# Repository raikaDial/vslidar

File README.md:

# vslidar
A Low-Cost 3D Multi-LIDAR System for ROS

Future site of developed hardware, software, and firmware.

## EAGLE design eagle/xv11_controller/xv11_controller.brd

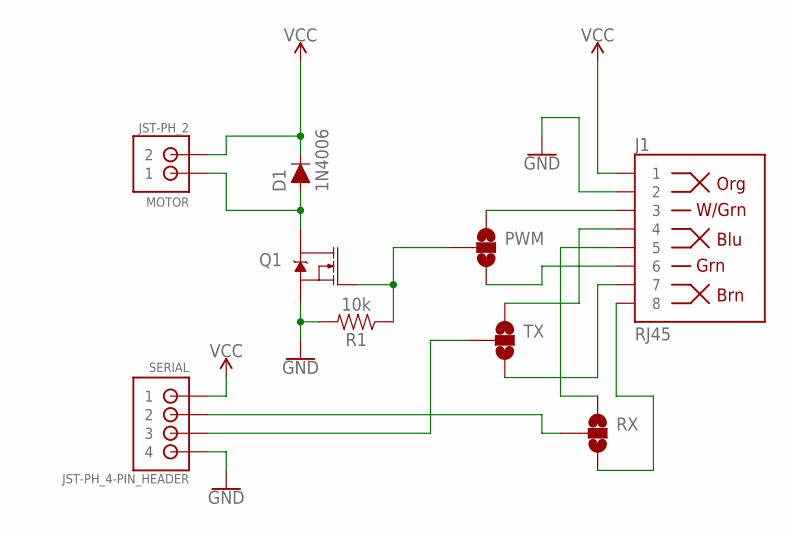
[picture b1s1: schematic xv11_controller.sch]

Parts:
D1: 1N4006; DIODE-1N4001
J1: RJ45; RJ45-8
MOTOR: JST-PH_2; JST_B2B-PH_HEADER
PWM: JUMPER-SMT_3_NO_NO-SILK; SMT-JUMPER_3_NO_NO-SILK
Q1: MOSFET-NCH-FQP30N06L; TO220V
R1: 10k; AXIAL-0.3
RX: JUMPER-SMT_3_NO_NO-SILK; SMT-JUMPER_3_NO_NO-SILK
SERIAL: JST-PH_4-PIN_HEADER; JST_B4B-PH_HEADER
TX: JUMPER-SMT_3_NO_NO-SILK; SMT-JUMPER_3_NO_NO-SILK

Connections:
GND: J1.2, Q1.3 (S), R1.P$2 (2), SERIAL.P4 (4)
unnamed: PWM.2, Q1.1 (G), R1.P$1 (1)
unnamed: D1.A, MOTOR.P1 (1), Q1.2 (D)
unnamed: J1.3, PWM.1
unnamed: J1.6, PWM.3
unnamed: J1.4, TX.1
unnamed: J1.7, TX.3
unnamed: J1.5, RX.1
unnamed: J1.8, RX.3
RX: RX.2, SERIAL.P2 (2)
TX: SERIAL.P3 (3), TX.2
VCC: D1.C, J1.1, MOTOR.P2 (2), SERIAL.P1 (1)

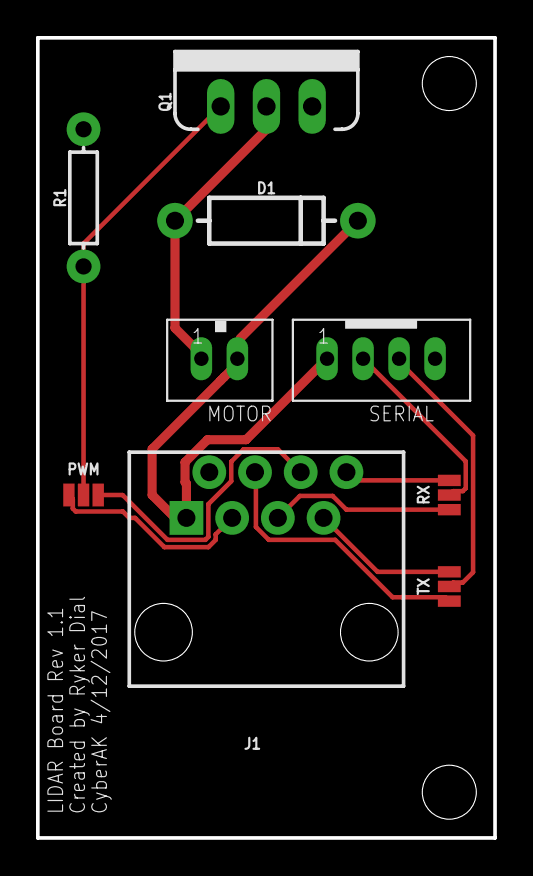
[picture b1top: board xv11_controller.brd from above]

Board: 2 copper layers, 25.4 x 44.5 mm, 9 parts (0 on the bottom side), 12 nets.

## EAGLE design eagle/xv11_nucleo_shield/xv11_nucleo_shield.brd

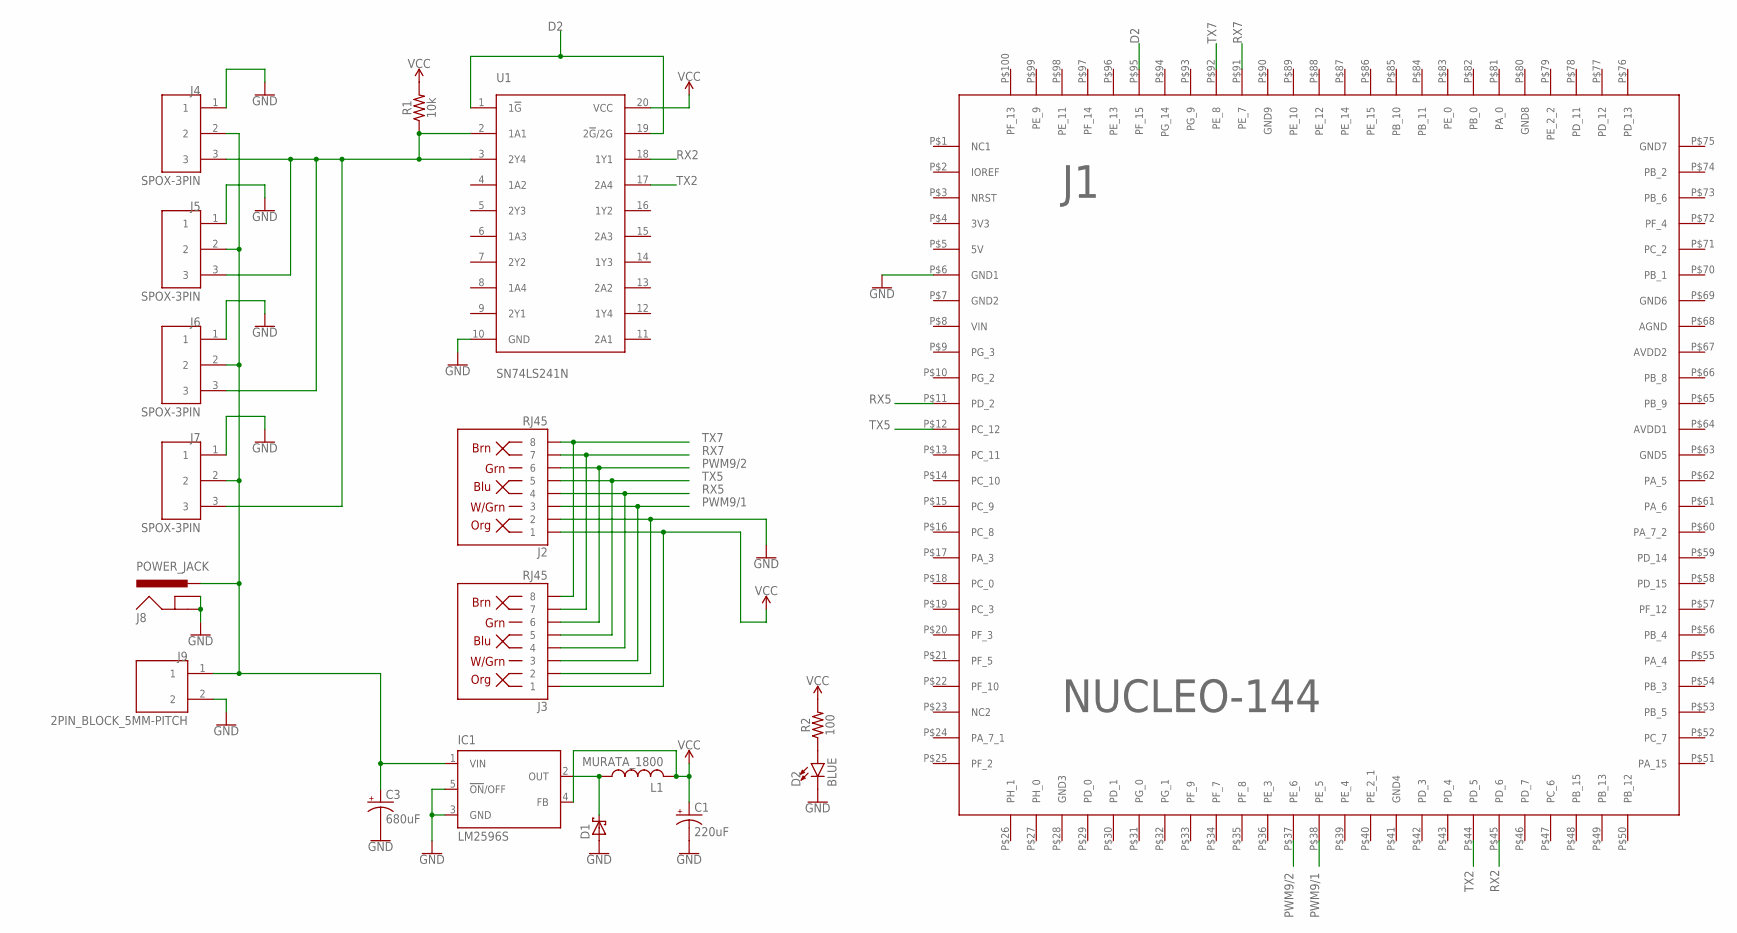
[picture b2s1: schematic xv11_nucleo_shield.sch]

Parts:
C1: 220uF; CPOL-RADIAL-2.5MM-6.5MM
C3: 680uF; EEU-FR1C681L
D1: SCHOTTKY-DIODEDO201T15; DO201T15
D2: BLUE; LED-1206
IC1: LM2596S; TO263-5
J1: NUCLEO-144
J2, J3: RJ45; RJ45-8
J4, J5, J6, J7: SPOX-3PIN
J8: POWER_JACK; POWER_JACK_PTH
J9: 2PIN_BLOCK_5MM-PITCH
L1: MURATA_1800
R1: 10k; AXIAL-0.3
R2: 100; AXIAL-0.3
U1: SN74LS241N; DIL20

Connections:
D2: J1.P$95 (PF_15), U1.1 (1!G), U1.19 (2!G!/2G)
GND: C1.2 (-), C3.P$2 (-), D1.A, D2.C, IC1.3 (GND), IC1.5 (!ON!/OFF), J1.P$6 (GND1), J2.2, J3.2, J4.1, J5.1, J6.1, J7.1, J8.GND, J8.GNDBREAK, J9.2, U1.10 (GND)
unnamed: J4.3, J5.3, J6.3, J7.3, R1.P$1 (1), U1.2 (1A1), U1.3 (2Y4)
unnamed: C3.P$1 (+), IC1.1 (VIN), J4.2, J5.2, J6.2, J7.2, J8.PWR, J9.1
unnamed: D1.C, IC1.2 (OUT), L1.P$1 (1)
unnamed: D2.A, R2.P$1 (1)
PWM9/1: J1.P$38 (PE_5), J2.3, J3.3
PWM9/2: J1.P$37 (PE_6), J2.6, J3.6
RX2: J1.P$45 (PD_6), U1.18 (1Y1)
RX5: J1.P$11 (PD_2), J2.4, J3.4
RX7: J1.P$91 (PE_7), J2.7, J3.7
TX2: J1.P$44 (PD_5), U1.17 (2A4)
TX5: J1.P$12 (PC_12), J2.5, J3.5
TX7: J1.P$92 (PE_8), J2.8, J3.8
VCC: C1.1 (+), IC1.4 (FB), J2.1, J3.1, L1.P$2 (2), R1.P$2 (2), R2.P$2 (2), U1.20 (VCC)

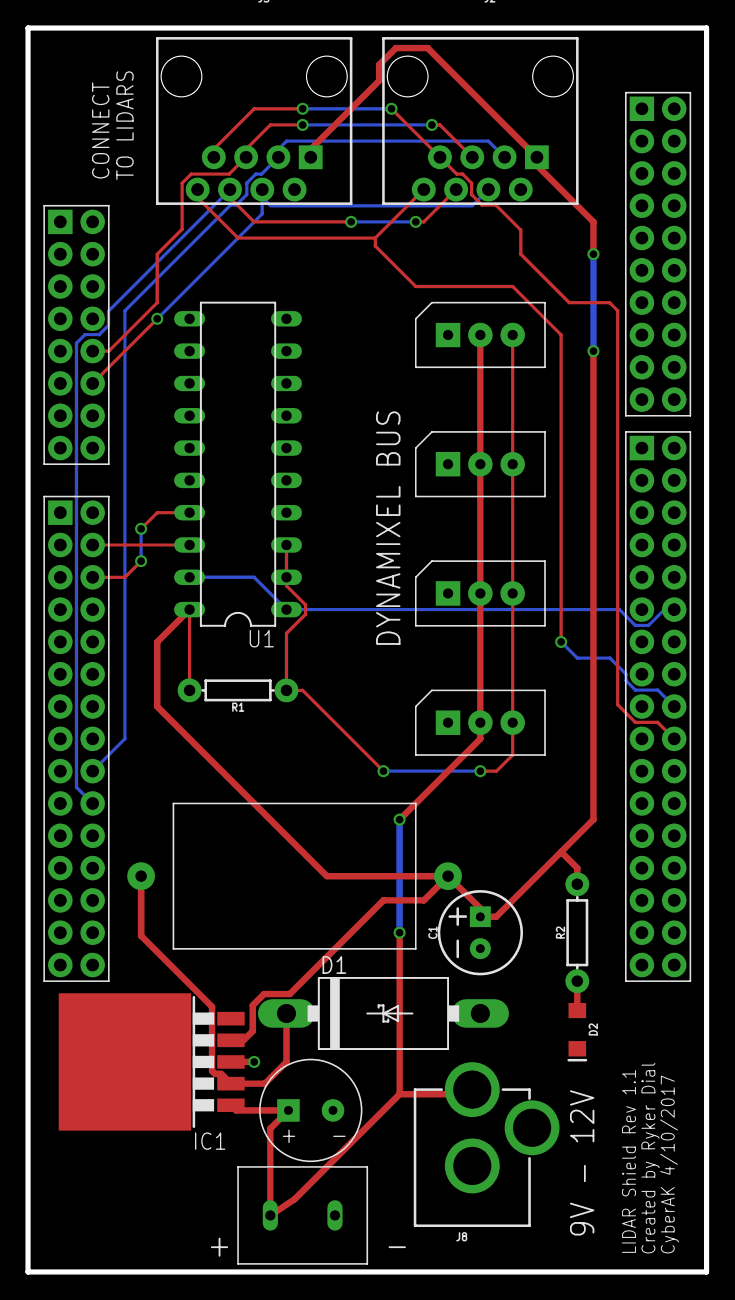
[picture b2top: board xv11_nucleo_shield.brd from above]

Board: 2 copper layers, 53.3 x 97.8 mm, 18 parts (0 on the bottom side), 15 nets.

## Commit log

2018-07-29 Added thesis.
2018-08-07 Transfer files to public repo.

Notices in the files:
parts and their libraries:
SparkFun-DiscreteSemi: Licensing: Creative Commons ShareAlike 4.0 International - https://creativecommons.org/licenses/by-sa/4.0
